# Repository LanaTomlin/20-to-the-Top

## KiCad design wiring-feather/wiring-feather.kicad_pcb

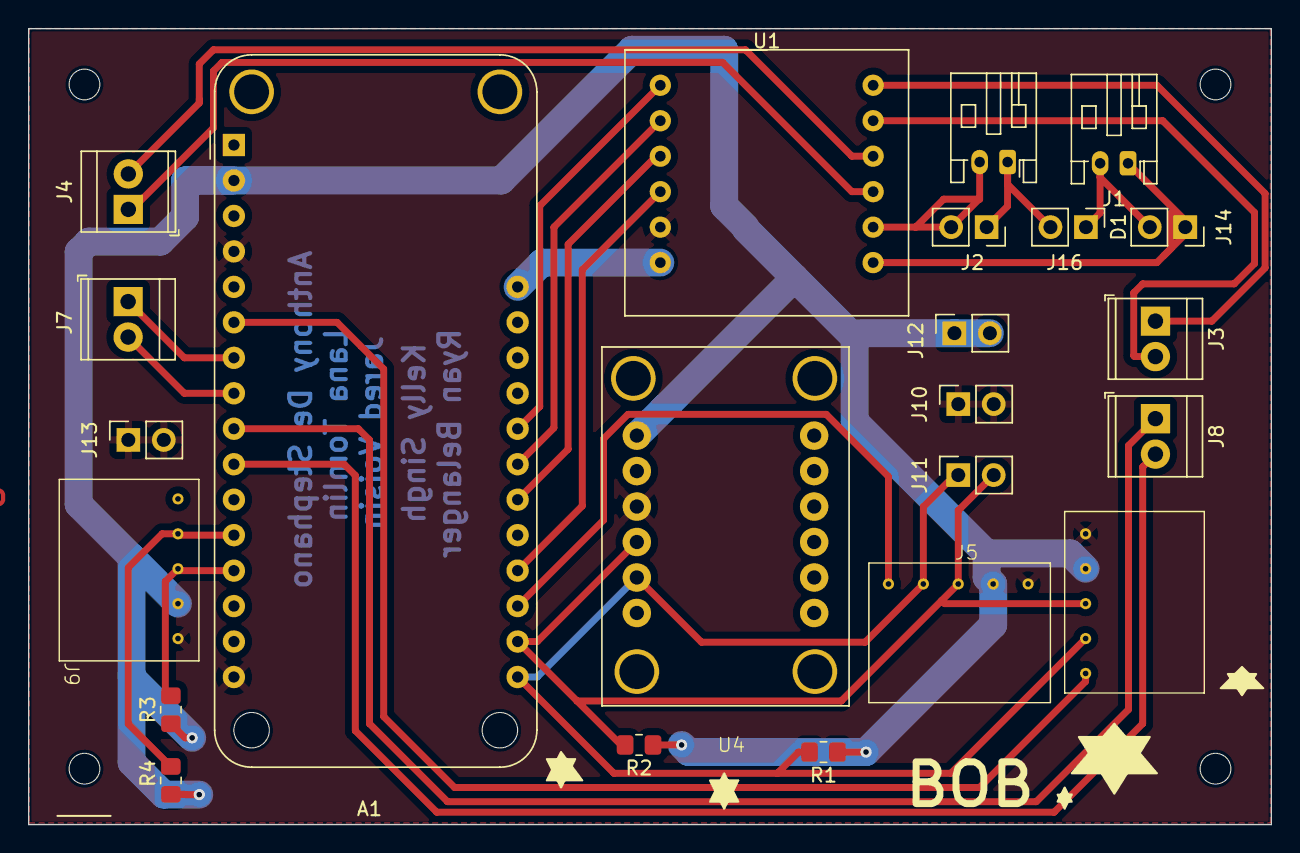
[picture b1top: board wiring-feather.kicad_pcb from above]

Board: 2 copper layers, 89.0 x 57.0 mm, 24 parts (0 on the bottom side), 25 nets.

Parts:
A1: Adafruit_Feather_M0_Adalogger
D1: D; PinHeader_1x02_P2.54mm_Vertical
J1, J2: M Battery 1; JST_PH_S2B-PH-K_1x02_P2.00mm_Horizontal
J3: PWR M1; Screw_terminal_TE_Connectivity
J4: Screw_Terminal_01x02; Screw_terminal_TE_Connectivity
J5: TOF RESET; JST_breakout
J6: TOF INT; JST_breakout
J7: ENC M2; Screw_terminal_TE_Connectivity
J8: ENC M1; Screw_terminal_TE_Connectivity
J9: TOF DNP [BACK-UP]; JST_breakout
J10: GND_TEST; PinSocket_1x02_P2.54mm_Vertical
J11: I2C_TEST; PinSocket_1x02_P2.54mm_Vertical
J12: 3V3; PinSocket_1x02_P2.54mm_Vertical
J13: GND; PinSocket_1x02_P2.54mm_Vertical
J14: BATT2-Charge; PinSocket_1x02_P2.54mm_Vertical
J16: BATT1-Charge; PinSocket_1x02_P2.54mm_Vertical
R1, R2, R3, R4: 10k; R_0805_2012Metric_Pad1.20x1.40mm_HandSolder
REF: MountingHole_2.2mm_M2
U1: TB6612FNG-Breakout; DRI0044
U4: ICM-20948-Adafruit; ICM-20948

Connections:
+3V3: A1.2 (3V3), J5.4, J6.4, J9.4, J12.1, J12.2, R1.1, R2.1, R3.1, R4.1, U4.1 (VIN)
/1BATT+: D1.2 (A), J2.1, J16.1
/1BATT_: J2.2, J16.2, U1.8 (GND)
/2BATT+: J1.1, J14.1, U1.7 (VM(<12V))
/2BATT_: D1.1 (K), J1.2, J14.2
/DIR1-M1: A1.24 (D12), U1.1 (DIR1)
/DIR1-M2: A1.20 (D6), U1.4 (DIR2)
/ENCA_M1: A1.9 (A4), J8.1
/ENCA_M2: A1.8 (A3), J7.2
/ENCB_M1: A1.10 (A5), J8.2
/ENCB_M2: A1.7 (A2), J7.1
/INT: A1.6 (A1), J6.1
/MCU_BAT+: A1.28 (VBAT), U1.6 (VCC)
/NEG_M1: J3.2, U1.11 (M1-)
/NEG_M2: J4.1, U1.9 (M2-)
/PWM-M1: A1.23 (D11), U1.2 (PWM1)
/PWM-M2: A1.22 (D10), U1.3 (PWM2)
/PWR_M1: J3.1, U1.12 (M1+)
/PWR_M2: J4.2, U1.10 (M2+)
/RESET: A1.19 (D5), J5.1
/SCL: A1.18 (SCL/D21), J5.3, J6.3, J11.2, R2.2, U4.4 (SCL/SCLK)
/SCL_2: A1.13 (MISO/D22), J9.3, R3.2
/SDA: A1.17 (SDA/D20), J5.2, J6.2, J11.1, R1.2, U4.5 (SDA/SDI)
/SDA_2: A1.12 (MOSI/D23), J9.2, R4.2
GND: A1.4 (GND), A1.16 (GND), J5.5, J6.5, J9.5, J10.1, J10.2, J13.1, J13.2, U1.5 (GND), U4.3 (GND)

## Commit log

2023-01-18 copied over base code from similar project
2023-01-18 removed uneccessary stuff from schematic
2023-01-30 cheap sensors
2023-02-14 updated wiring diagram with proper power
2023-02-15 updated some connectors and power connections
2023-02-16 Fixed library issues for feather, added feather schematic
2023-02-17 Some small changes footprint library
2023-02-18 add symbol and footprint libraries
2023-02-18 Created footprint for the feather
2023-02-19 Created footprint for components
    All components have footprints, approx for the IMU, auto placed them on the PCB
2023-02-19 made rough pcb
2023-02-20 updated pcb
2023-02-20 Added testing points, i2c pullup resistors
2023-03-06 design checks and silkscreen done
